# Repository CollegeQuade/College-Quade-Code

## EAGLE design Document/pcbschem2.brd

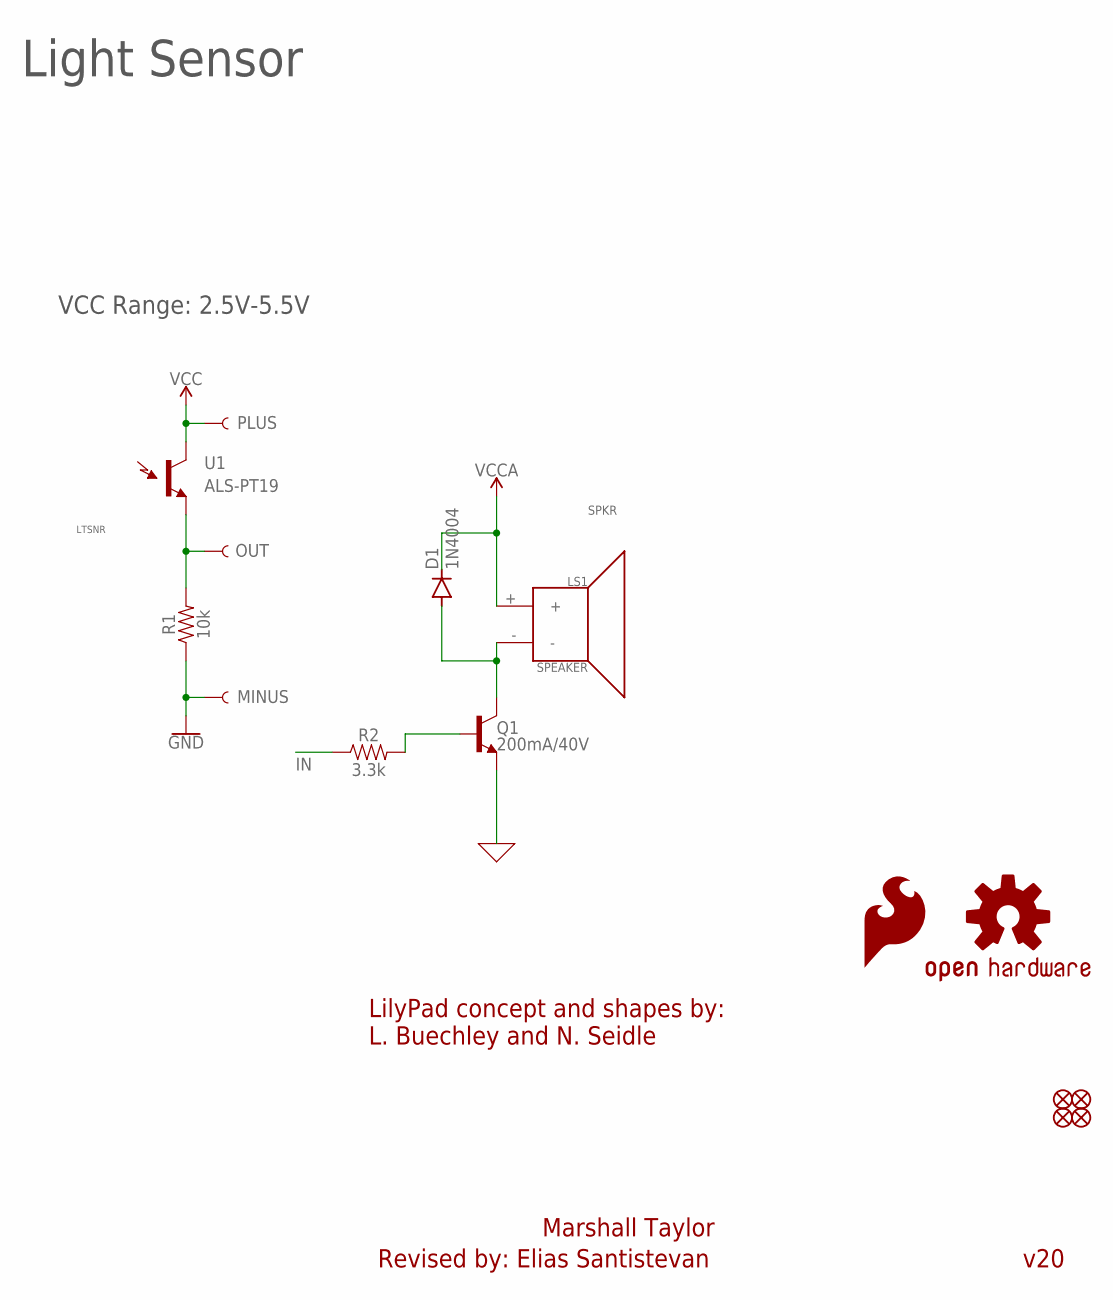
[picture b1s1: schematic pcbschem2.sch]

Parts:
D1: 1N4004; DO41-10
FD1, FD2, FD3, FD4: FIDUCIALUFIDUCIAL; FIDUCIAL-MICRO
LOGO1: OSHW-LOGOMINI; OSHW-LOGO-MINI
LOGO2: SFE_LOGO_FLAME.1_INCH; SFE_LOGO_FLAME_.1
LS1: SPEAKER; PCB_MOUNT_SPEAKER
Q1: 200mA/40V; TO-92
R1: 10k; 0603
R2: 3.3k; 0603
SEWTAPLS+: PLUS; PETAL-SMALL-2SIDE
SEWTAPLS-: MINUS; PETAL-SMALL-2SIDE
SEWTAPLSOUT: OUT; PETAL-SMALL-2SIDE
U1: ALS-PT19

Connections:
0: Q1.1 (E)
3.3V: SEWTAPLS+.1, U1.C (C1)
GND: R1.1, SEWTAPLS-.1
IN: R2.1
LTSNR: R1.2, SEWTAPLSOUT.1, U1.E (E1)
unnamed: Q1.2 (B), R2.2
unnamed: D1.A, LS1.-, Q1.3 (C)
SPKR: D1.C, LS1.+

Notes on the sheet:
Light Sensor
Marshall Taylor
v20
Revised by: Elias Santistevan
VCC Range: 2.5V-5.5V
LilyPad concept and shapes by: L. Buechley and N. Seidle

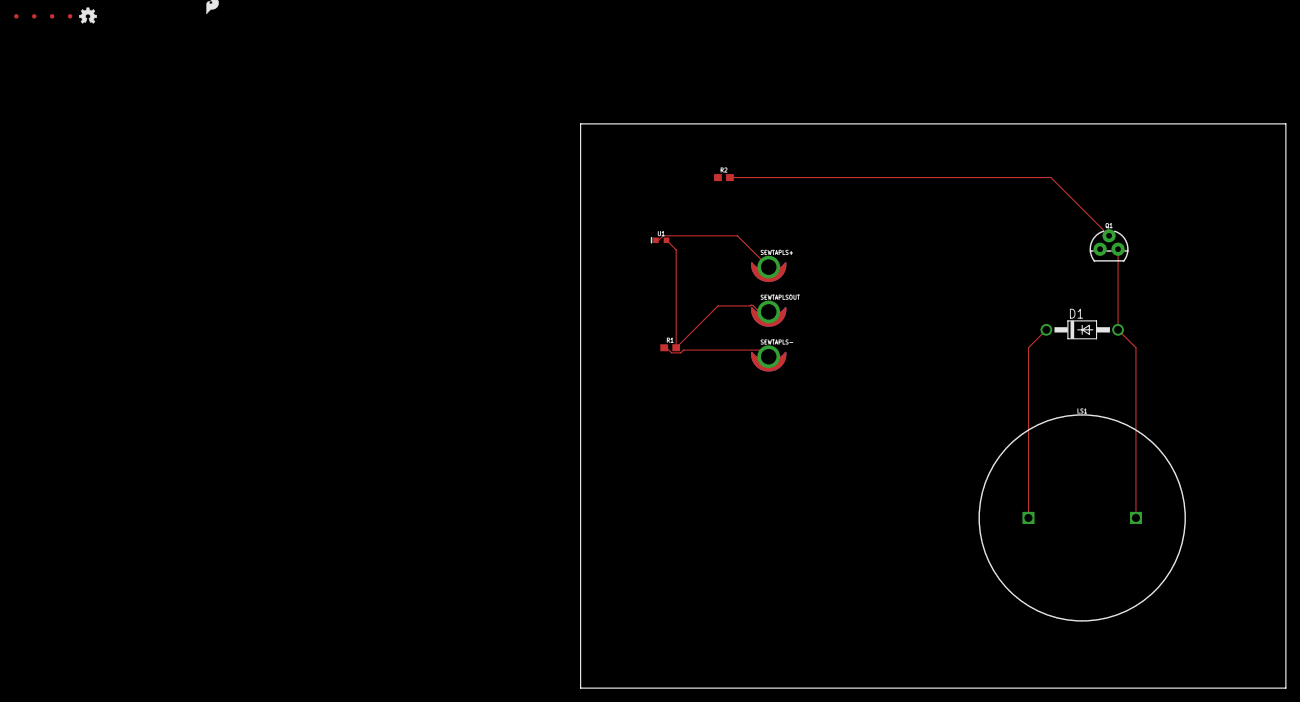
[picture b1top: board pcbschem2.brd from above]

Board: 2 copper layers, 100.0 x 80.0 mm, 15 parts (0 on the bottom side), 6 nets.

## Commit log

2020-11-02 Create code
2020-11-02 Rename code to i2c.c
2020-11-08 Add files via upload
    these are from the PCA9685 files the professor shared a couple of days ago on discord in "IMU_TestBench"
2020-11-11 Create outline
    trying to make the different states for the main.c
2020-11-11 Rename servo.h to xyzservo.h
2020-11-11 Rename servo.c to xyzservo.c
2020-11-11 Add files via upload
    these are the servo files from the IMU testbench zip file but I changed the names for the servos and added functions for "standing still" and "walking", there are only 8 servos so this should work wi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
2020-11-13 Update servo.c
    added adjusting the buzzer volume into the function that makes quade walk so it repeats for as many steps as we want before finishing and going back to main
2020-11-13 Create main.c
    I tried filling in the outline for main.c but it still needs the code for the light sensor, interrupt, and ADC. Most of this is from the main.c included in the testbench.zip
2020-12-04 final product minus comments, newI2C replaces I2C, adc replaces half of the adc14_single_conversion_repeat and the rest goes into main, most pca content commented and adds printf statements
2020-12-04 Add files via upload
    adding the new files manually because of error trying to add the first time
2020-12-05 PCB_Files
2020-12-06 Datasheets
    Datasheets for the light sensor and buzzer we used
2020-12-06 Create new folder
2020-12-06 Document Folder
2020-12-06 Rename adc.c to code
2020-12-06 Rename adc.h to Code/adc.h
2020-12-06 Rename code to Code/adc.c
2020-12-06 Rename main.c to Code/main.c
2020-12-06 Rename newI2C.c to Code/newI2C.c
2020-12-06 Rename newI2C.h to Code/newI2C.h
2020-12-06 Rename pca.c to Code/pca.c
2020-12-06 Rename pca.h to Code/pca.h
2020-12-06 Rename servo.c to Code/servo.c
2020-12-06 Rename servo.h to Code/servo.h
2020-12-06 Rename system_msp432p401r.c to Code/system_msp432p401r.c
2020-12-06 Rename msp432p401r.cmd to Code/msp432p401r.cmd
2020-12-06 Rename pcbschem2.brd to Document/pcbschem2.brd
2020-12-06 Rename pcbschem2.sch to Document/pcbschem2.sch
2020-12-06 Light_Sensor_Datasheet
2020-12-06 Buzzer_Datasheet
2020-12-06 PCA9685
2020-12-06 added comments
2020-12-06 added comments and deleted unneeded port5 irq
2020-12-06 add credit to changes
2020-12-06 adding leveraged code
2020-12-06 add leveraged code to documentation

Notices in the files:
parts and their libraries:
SparkFun-Aesthetics: Licensing: CC v3.0 Share-Alike You are welcome to use this library for commercial purposes.
SparkFun-Electromechanical: Licensing: Creative Commons ShareAlike 4.0 International - https://creativecommons.org/licenses/by-sa/4.0
